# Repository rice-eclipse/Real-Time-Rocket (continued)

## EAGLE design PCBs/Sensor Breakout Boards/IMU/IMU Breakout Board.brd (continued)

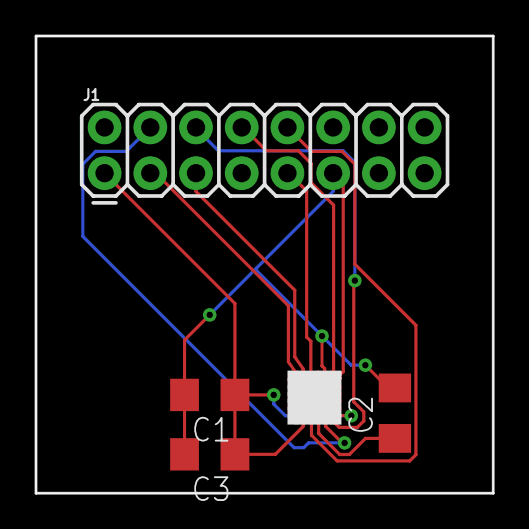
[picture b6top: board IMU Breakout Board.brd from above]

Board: 2 copper layers, 25.4 x 25.4 mm, 5 parts (0 on the bottom side), 10 nets.

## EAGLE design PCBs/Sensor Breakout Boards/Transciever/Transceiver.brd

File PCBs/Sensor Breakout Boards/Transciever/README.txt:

Breakout Board for the HOPERF transceiver (RFM95).
Used to test the transceiver without actually placing it onto our main Real Time Rocket Board.
Designed in EAGLE by Kevin Mejia
Project File- eagle.epf
Schematic- Transceiver schematic.sch
Board Layout- Transceiver schematic.brd

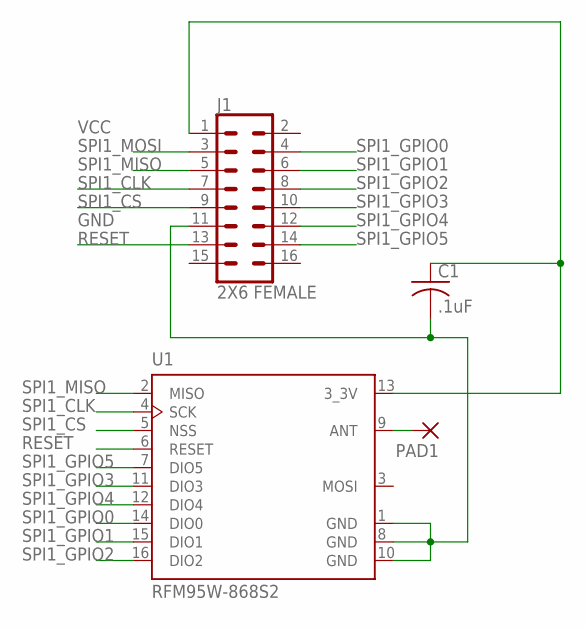
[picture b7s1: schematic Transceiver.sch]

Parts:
C1: .1uF; C1206
J1: 2X6 FEMALE; 2X7
PAD1: 2,54/1,0
U1: RFM95W-868S2; XCVR_RFM95W-868S2

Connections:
GND: C1.2, J1.11, U1.1 (GND), U1.8 (GND), U1.10 (GND)
unnamed: PAD1.1, U1.9 (ANT)
RESET: J1.13, U1.6 (RESET)
SPI1_CLK: J1.7, U1.4 (SCK)
SPI1_CS: J1.9, U1.5 (NSS)
SPI1_GPIO0: J1.4, U1.14 (DIO0)
SPI1_GPIO1: J1.6, U1.15 (DIO1)
SPI1_GPIO2: J1.8, U1.16 (DIO2)
SPI1_GPIO3: J1.10, U1.11 (DIO3)
SPI1_GPIO4: J1.12, U1.12 (DIO4)
SPI1_GPIO5: J1.14, U1.7 (DIO5)
SPI1_MISO: J1.5, U1.2 (MISO)
SPI1_MOSI: J1.3
VCC: C1.1, J1.1, U1.13 (3_3V)

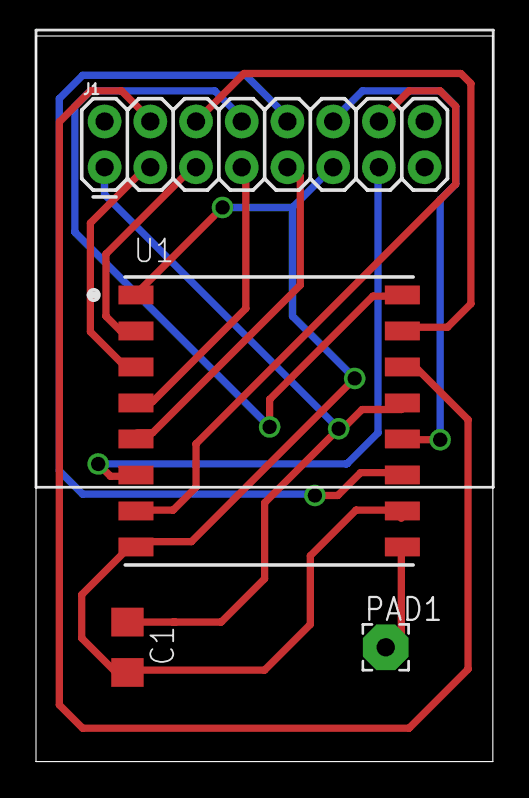
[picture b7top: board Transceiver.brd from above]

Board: 2 copper layers, 25.4 x 40.3 mm, 4 parts (0 on the bottom side), 13 nets.

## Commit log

2018-10-26 Initial commit for Real-Time-Rocket
2018-10-26 Initial Commit pt 2
2018-10-26 Rename Reciever_Code.ino to Reciever.ino
2018-10-26 Rename Transmitter_Code.ino to Transmitter.ino
2018-11-08 Added barebones transmission test for certs
    Just transmits incrementing numbers as fast as possible and logs to
    local SD. Receiver prints values to serial but does not log to any
    external source yet. Kept original factory examples in Examples folder.
2018-11-08 Added pressure/altitude/temperature sensor
2018-11-09 Created a local logging script
    Alternative to simply copy-pasting from Arduino serial monitor.
    Requires the Processing language to be installed. Put it on Hammer,
    might come in handy for the certs test.
2018-11-10 Now creates a new logfile on every run
2019-01-25 Changed Altitude function call from AltitudeFt to getAltitude
2019-01-25 Added faster transmitter code
2019-03-01 Changed pin definitions to keep consistent with Transmitter code
2019-08-13 Folder restructuring
2019-08-14 Added libraries and components for RTR
2019-08-16 Add battery holder library file
2019-08-16 Slight verification and modification of library files
2019-08-20 Add main RTR schematic (missing extra Li-Po power circuitry)
2019-08-22 Finalize schematic
2019-08-22 Add power circuitry libraries and update part footprints
2019-08-22 Add reference datasheets
2019-08-22 Update datasheets, small schematic revisions, add test pins
2019-08-24 Lay out components logically on board, miscellaneous library and schematic additions and fixes
2019-08-30 Route Board
2019-08-31 Increase size of and reroute VCC and VCC_5V traces throughout the board
2019-08-31 Update EAGLE version and small miscellaneous documentation/functionality fixes
2019-08-31 Add CAM file for ordering
2019-09-14 Added IMU datasheet
2019-09-21 Add Antenova datasheets
2019-09-21 Add symbol for M20050-1 gps
2019-09-22 initialize imu breakout project (port and imu components made)
2019-09-22 Update file names
2019-09-28 Add m20050-1 device in EAGLE
2019-09-29 added accel code
2019-10-11 Initial Commit for Transmitter code for ProtoV1
2019-10-12 Update libraries and add all sensor support
2019-10-16 Add zero calibration
2019-10-16 Clean up unnecessary files
2019-10-16 Update gitignore
2019-10-16 Add Kevin's Transciever breakout board
2019-10-16 Update names
2019-10-16 Add PCB Mill Design Rules
2019-10-19 Antenova GPS ready for mfg
2019-10-21 Add ground planes
2019-10-26 altimeter pcb files
2019-11-07 Restructure Proto folders and clean up unnecessary files
2019-11-07 Add IMU sensor library and support
2019-11-09 Add IMU Library
2019-11-09 Update packet formatting and drastic improvements to transmission rate
2019-11-09 Remove unnecessary precursor text
2019-11-14 Update packet length
2020-01-19 Add extra characters so message not cut off
2020-02-09 Reading numbers off of altimeter
2020-02-15 Improved data parsing
2020-02-23 Add remaining Sensor Breakout Boards
2020-03-05 Working pressure sensor
2020-03-05 Saved pocketbeagle files from a lost SD card
2020-03-05 git was weird
2020-10-03 Starting to rewrite code for transmitter
2020-10-03 Message byte count is only 251 :(
2020-11-07 Update Reciever.ino
    bye bye servo code
2021-02-13 Add RPI Zero W library
2021-02-13 Add sensor breakout boards
2021-02-14 Fixed a few mistakes in sensor breakouts
2021-02-14 Transceiver added to Electro II
2021-02-21 start updated gps breakout
2021-02-21 Laid out rough PCB for Electro II
2021-02-22 Lots of progress on boost converter
2021-02-22 More details on boost converter
2021-02-22 Concept trace layouts
2021-02-22 Working on ground plane concept
2021-02-23 Added sample pins and new trace ideas
2021-02-28 Created ElectroII folder
2021-02-28 Tested I2C
2021-03-06 Altimeter testing
2021-03-08 IMU_BNO085_Schematic
    Beginning work
2021-03-08 Fixed MOSI/MISO mistake
2021-03-09 Revised IMU schematic and roughed out board
2021-03-10 Laid out board + redid library for BNO
2021-03-10 Cleaned up board, see Cleanup files
2021-03-14 altimeter breakout v2
2021-03-15 Updated RPi library
2021-03-15 Board shake-ups from design review
2021-03-15 More board shuffling
2021-03-20 Reviewed traces and fixed joints
2021-03-21 some cleanup
2021-03-21 Prep for JLC?
2021-03-21 gps suffering
2021-03-22 Schematic for BNO055
2021-03-22 Updated Sketch
2021-03-26 Moved the caps to actually be useful
2021-04-04 GPS2 schematic
2021-04-04 first draft of gps breakout 2
2021-04-11 finish gpsv2
2021-04-14 actually updated the imu board, might want to check clearance before shipping it out
2021-08-27 **NEW AND IMPROVED**
    new and improved versions for a 2021 fall
2021-08-27 gps for fabrication
2021-08-27 generate cam files
2021-10-26 update gps to work with smaller inductor
2021-10-29 modified altimeter.py, new altimeter run file
2021-11-23 added data storages functionality
2021-11-23 github sucks for updating password
2021-12-04 prep for first launch
2022-02-07 update gitignore pro files
2022-02-07 fix standby and gnd gps
2022-03-27 Buck converter instead of boost
    Hopefully it works
2022-04-10 fixed with erc and drc
    should be go to go
2022-11-10 made changes to schematic, see schematic notes doc in drive
2022-11-18 update 11_17
2022-11-23 Added layout version 1 11_23_22
2022-12-02 Neutro layout revision 12.2.22
2022-12-04 neutro layout update 12.4.22
2022-12-05 layout revision 12.4.22
2022-12-24 Revision 12.24.22
2022-12-24 Neutro revision 12.24.22
2023-01-21 neutro pcb v1 final design 1.21.22
2023-01-21 neutro v1 1.21.23 final pcb (change L2, L3 size)
2023-01-22 1.22.23 final neutro v1 pcb
2023-01-23 added electroII code
2023-02-06 Added folder for neutro code
2023-02-06 added example code for BNO085
2023-02-13 add altimeter and gps code for neutro from electroII reference
2023-02-21 added led blink test
2023-02-21 add git ignore and delete DS
2023-02-21 add DS_Store to .gitignore
2023-02-21 turn off light after blinking
2023-02-21 turn led off at end of blink test
2023-02-27 verified BOM
2023-02-27 remove ds store
2023-02-27 add altimeter code
2023-02-27 transceiver code
2023-02-27 change transceiver pin
2023-02-27 modified altimeter code
2023-03-03 chat gpt altimeter code
2023-03-03 print altitude
2023-03-03 slower measure frequency
2023-03-03 added gpt gps code
2023-03-03 change to pyserial
2023-03-03 add not fix
2023-03-03 open serial test
2023-03-03 added check if gps is on
2023-03-03 add imu code
2023-03-03 add timeout
2023-03-03 check imu status
2023-03-03 check imu status remove timeout
2023-03-03 imu code no timeout
2023-03-05 turn everything on
2023-03-05 added code found online
2023-03-05 disable turn all on
2023-03-06 turn serial options on
2023-03-06 change to AMA0
2023-03-06 added print statement
2023-03-06 removed some serial arguments
2023-03-06 add line read
2023-03-06 add data
2023-03-06 change to ttys0
2023-03-19 change altimeter units
2023-03-19 delay
2023-03-19 galveston pressure
2023-03-23 added 3.25.23 testing files
2023-03-23 added stadium transmit test
2023-03-23 change config file path
2023-03-23 fix tabs
2023-03-23 remove more tabs from yaml
2023-03-23 update adafruit rfm module used
2023-03-23 update transceiver pin
2023-03-23 update altimeter packet
2023-03-23 change yaml
2023-03-23 time_ns()
2023-03-23 some chnges to struct.pack
2023-03-23 add .items()
2023-03-23 used ms5803.py module
2023-03-23 added ms5803.py
2023-03-23 change pressure unit
2023-03-23 change sea level pressure
2023-03-24 gpio26 high mode
2023-03-24 print error in except block
2023-03-24 move GPIO cleanup to the end
2023-03-24 modified code to transmit with NARWAL
2023-03-24 blink 10 times
2023-03-24 blink 50 times at boot
2023-03-24 turn off led after 5 blinks
2023-03-24 blink 100 times on boot and adjust to galveston sea pressure
2023-04-06 added neutro using adafruit gps breakout
2023-04-06 remove non pcb related files, stored in other branches
2023-04-06 test
2023-04-10 update v2 pcb
2023-04-10 update gerber file
2023-04-10 verified gps module footprint
2023-04-10 finalize gerber for jlc
2023-05-10 kicad bom file
2023-05-11 testing altimeter on neutro 2
2023-05-22 adafruit gps code example
2023-05-22 adafruit gps code example change to serial
2023-05-22 rename gps python file name
2023-05-22 remove precision format
2023-05-22 comment trx on altimeter
2023-05-22 test green LED
2023-05-22 RTR sensor final code, transmission part to be updated
2023-05-22 led check
2023-05-22 recheck led blink
2023-05-22 note on imu not working
2023-06-26 added folder for supplementary files such as JLC order setting, datasheets, and KICAD symbol footprint files
2023-08-21 Create README.md
    Added Neutro description
2023-08-21 Create README.md
    Added neutro 2 description
2023-08-21 Create README.md
    add neutro board description
